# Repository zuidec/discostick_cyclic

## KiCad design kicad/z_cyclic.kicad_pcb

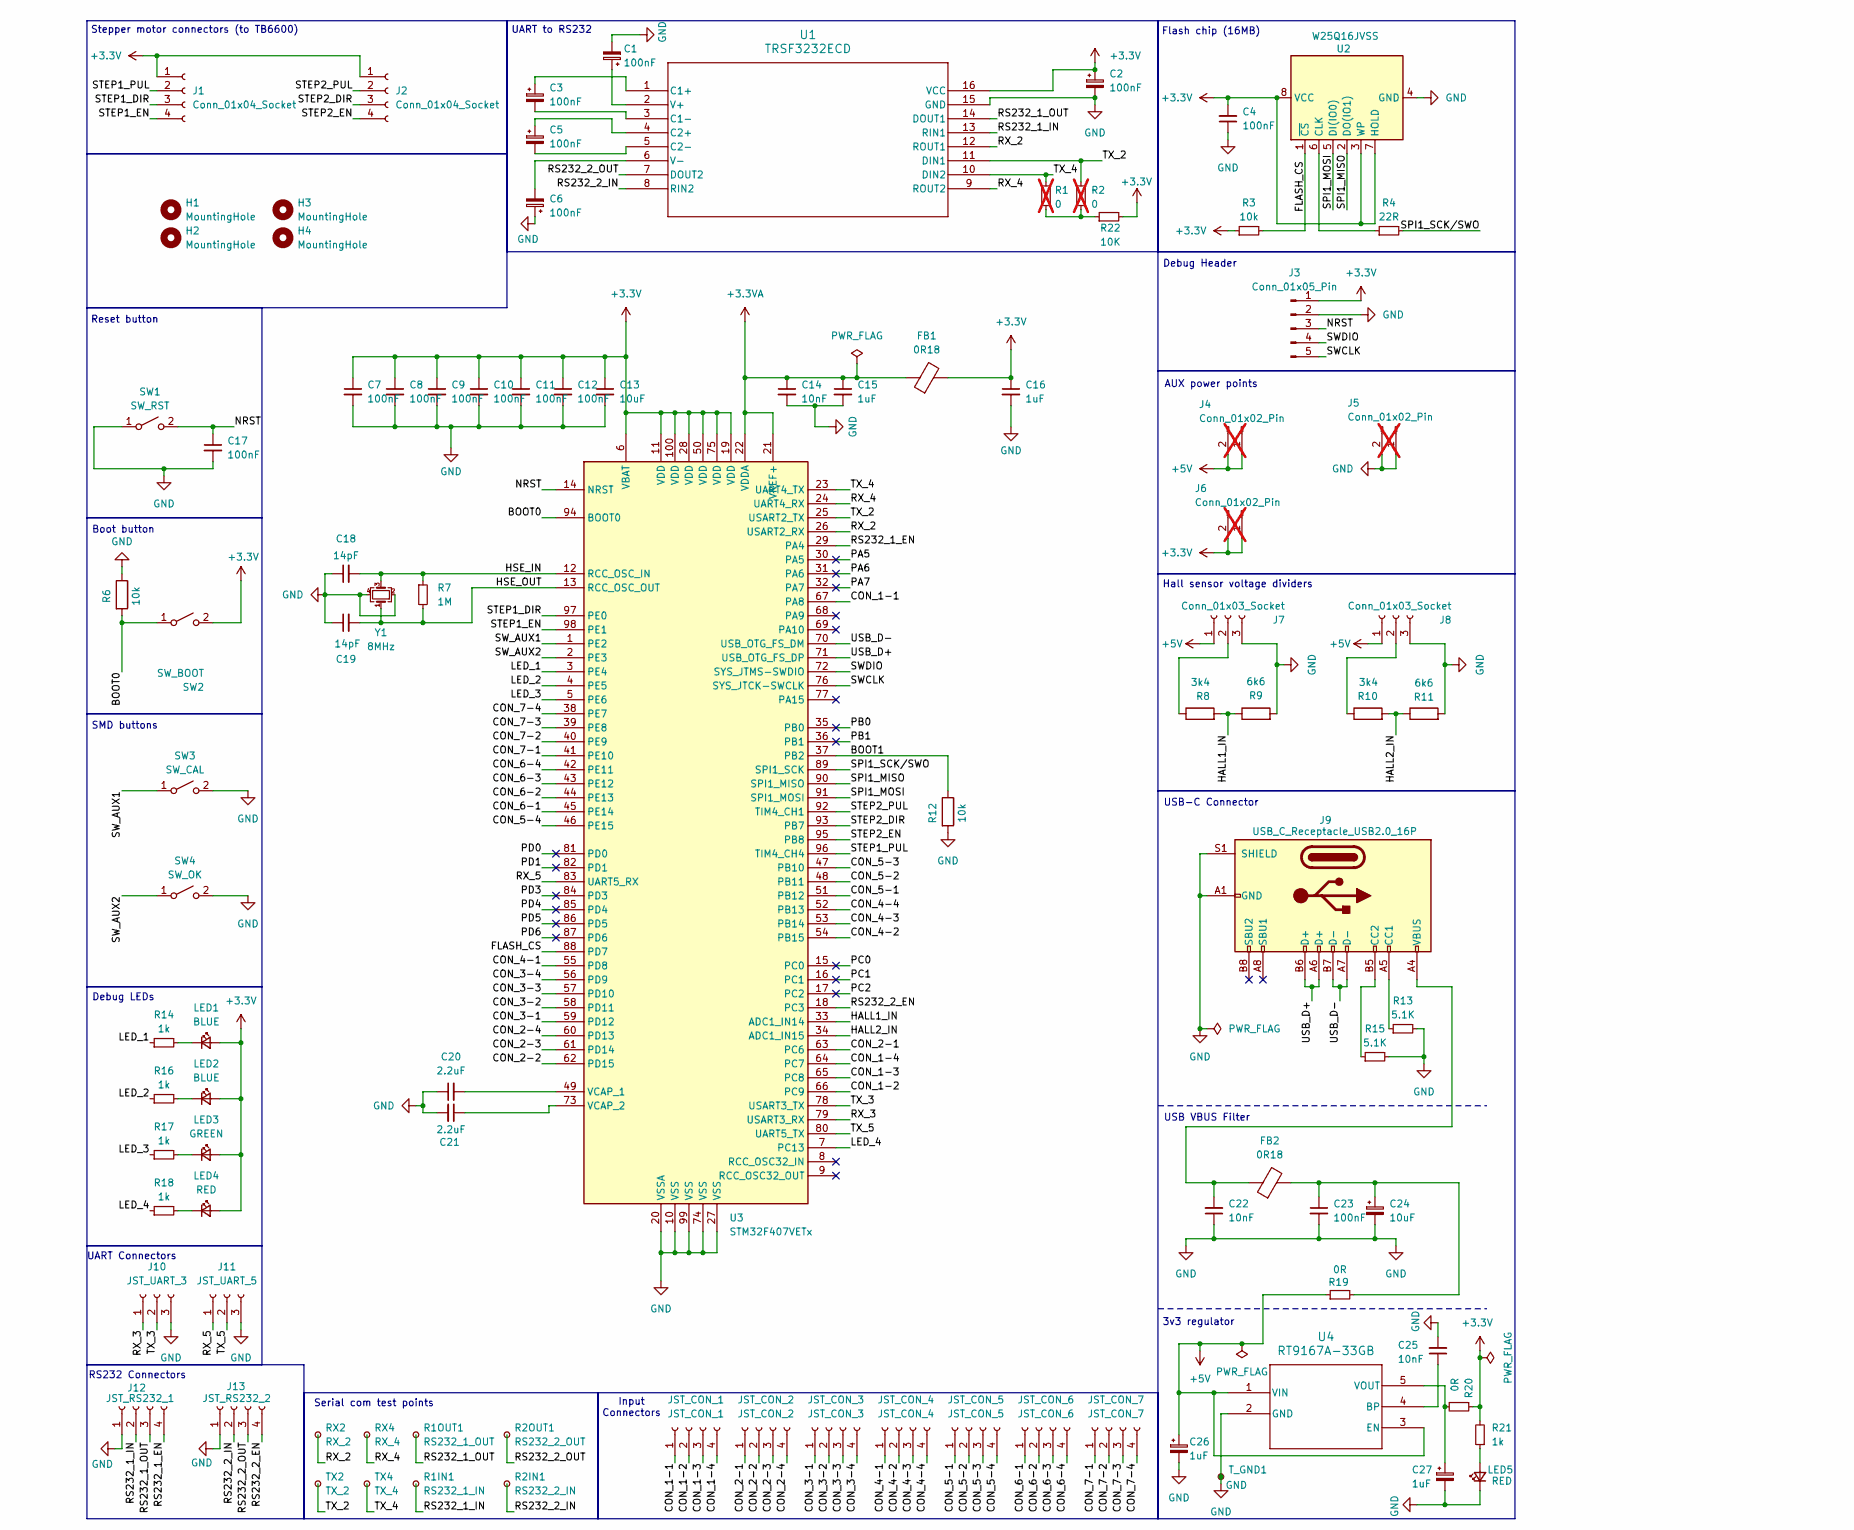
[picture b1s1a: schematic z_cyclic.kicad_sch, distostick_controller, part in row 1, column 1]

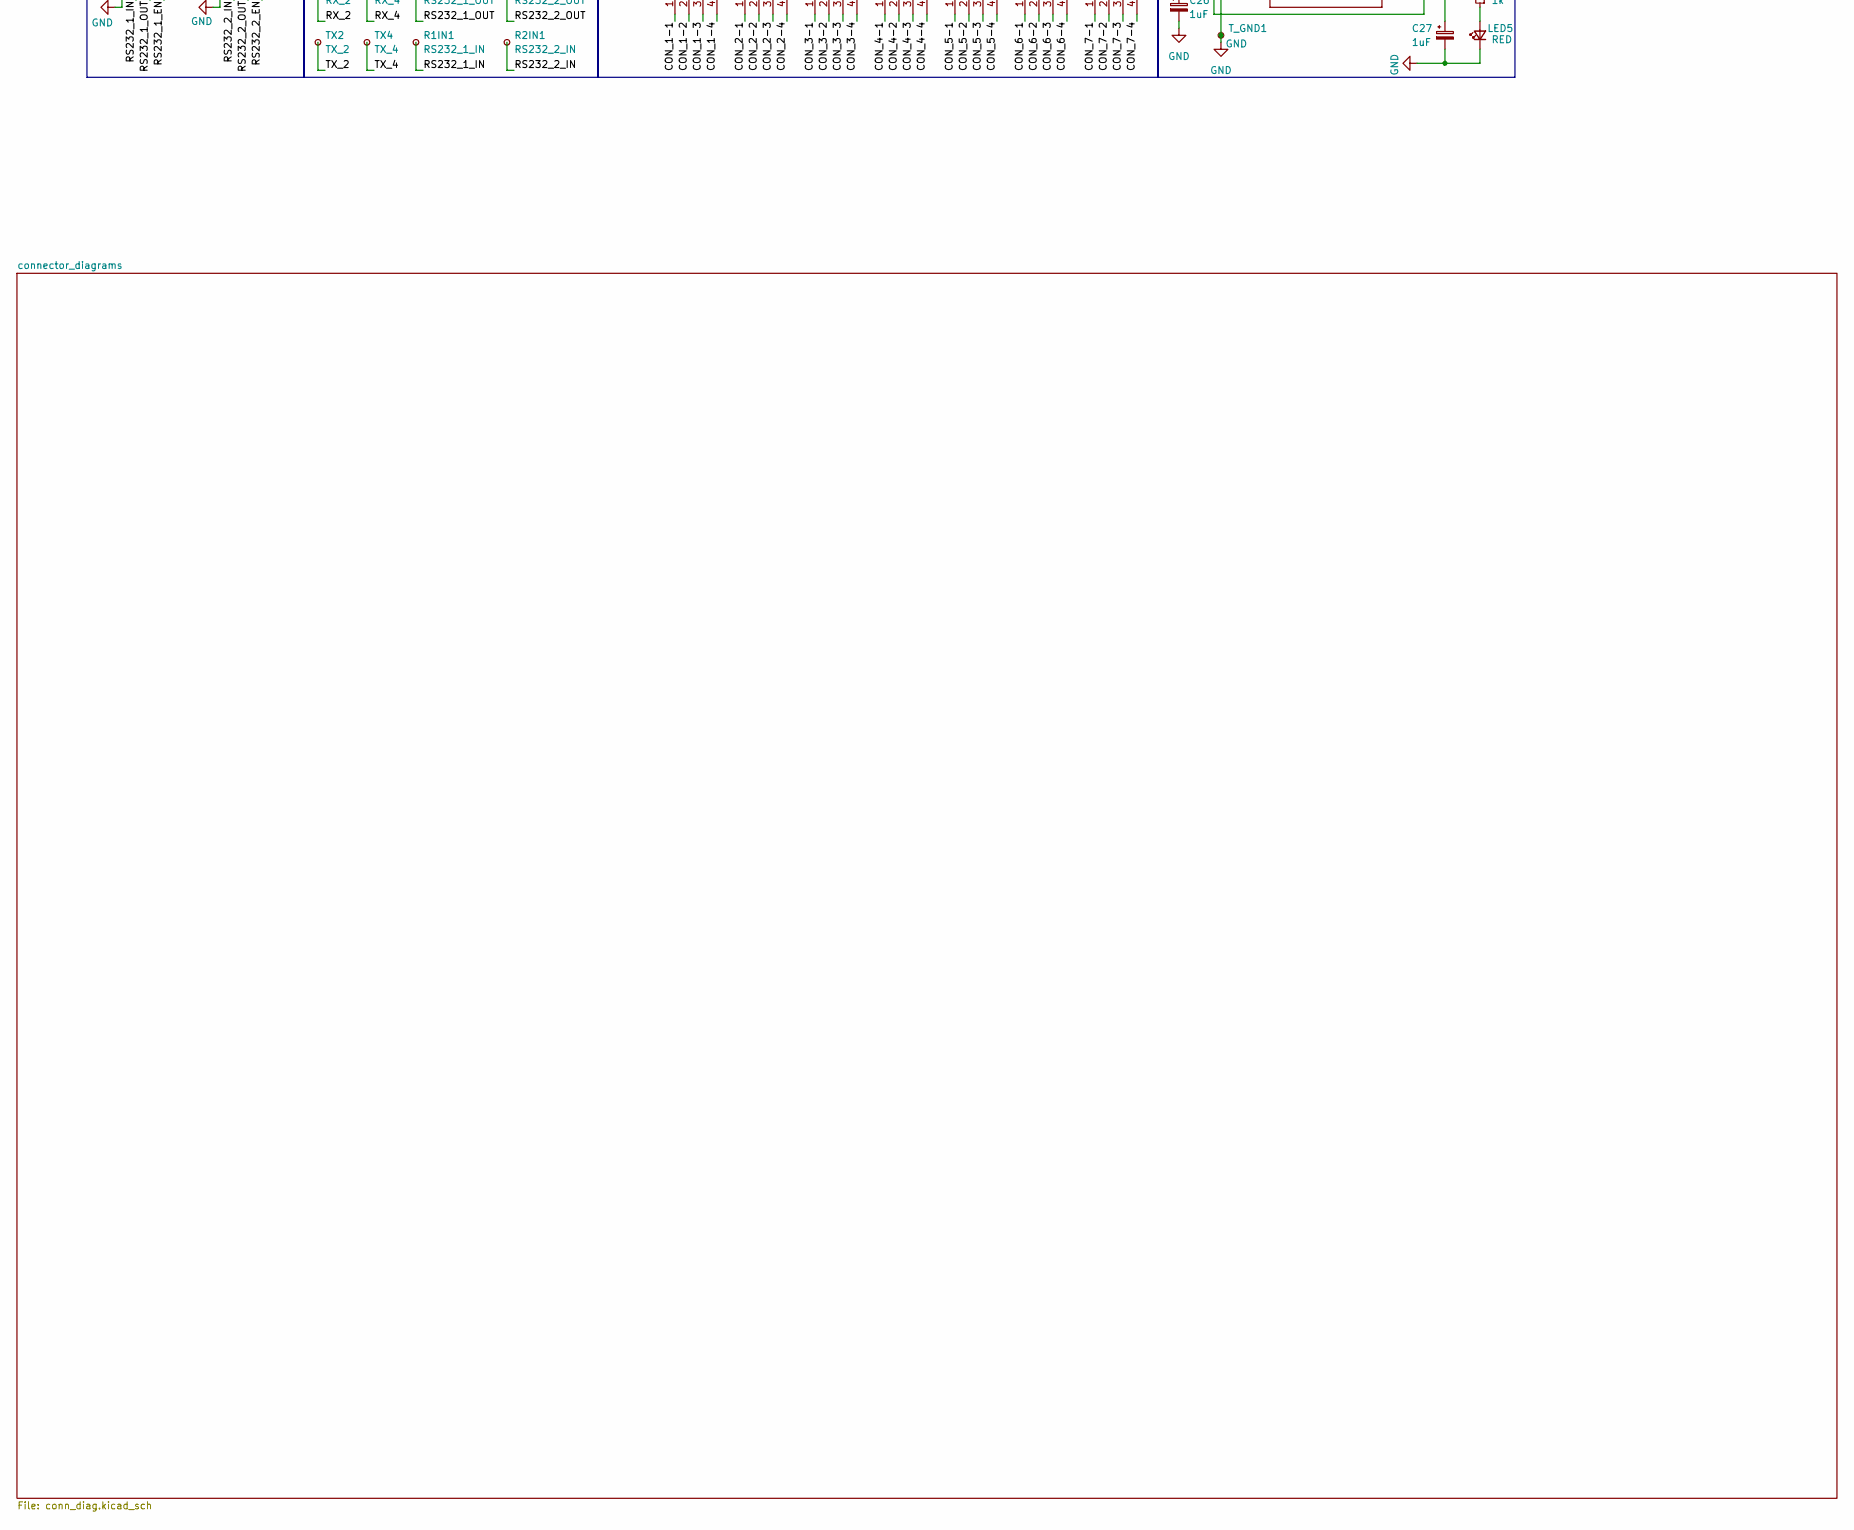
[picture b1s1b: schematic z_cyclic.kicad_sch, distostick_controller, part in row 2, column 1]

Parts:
C1, C2, C3, C4, C5, C6, C7, C8, C9, C10, C11, C12, C17, C23: 100nF; C_0402_1005Metric
C13, C24: 10uF; C_0603_1608Metric
C14, C22, C25: 10nF; C_0402_1005Metric
C15, C16, C26: 1uF; C_0402_1005Metric
C18, C19: 14pF; C_0402_1005Metric
C20, C21: 2.2uF; C_0402_1005Metric
C27: 1uF; C_0603_1608Metric
FB1, FB2: 0R18; R_0805_2012Metric
H1, H2, H3, H4: MountingHole; MountingHole_3.2mm_M3
J1, J2: Conn_01x04_Socket; JST_EH_B4B-EH-A_1x04_P2.50mm_Vertical
J3: Conn_01x05_Pin; PinHeader_1x05_P2.54mm_Vertical
J4, J5, J6: Conn_01x02_Pin; PinSocket_1x02_P2.54mm_Vertical; not fitted
J7, J8: Conn_01x03_Socket; JST_EH_B3B-EH-A_1x03_P2.50mm_Vertical
J9: USB_C_Receptacle_USB2.0_16P; USB_C_Receptacle_G-Switch_GT-USB-7010ASV
J10: JST_UART_3; JST_EH_B3B-EH-A_1x03_P2.50mm_Vertical
J11: JST_UART_5; JST_EH_B3B-EH-A_1x03_P2.50mm_Vertical
J12: JST_RS232_1; JST_EH_B4B-EH-A_1x04_P2.50mm_Vertical
J13: JST_RS232_2; JST_EH_B4B-EH-A_1x04_P2.50mm_Vertical
JST_CON_1: JST_CON_1; JST_EH_B4B-EH-A_1x04_P2.50mm_Vertical
JST_CON_2: JST_CON_2; JST_EH_B4B-EH-A_1x04_P2.50mm_Vertical
JST_CON_3: JST_CON_3; JST_EH_B4B-EH-A_1x04_P2.50mm_Vertical
JST_CON_4: JST_CON_4; JST_EH_B4B-EH-A_1x04_P2.50mm_Vertical
JST_CON_5: JST_CON_5; JST_EH_B4B-EH-A_1x04_P2.50mm_Vertical
JST_CON_6: JST_CON_6; JST_EH_B4B-EH-A_1x04_P2.50mm_Vertical
JST_CON_7: JST_CON_7; JST_EH_B4B-EH-A_1x04_P2.50mm_Vertical
LED1, LED2: BLUE; LED_0402_1005Metric
LED3: GREEN; LED_0402_1005Metric
LED4, LED5: RED; LED_0402_1005Metric
R1, R2: 0; R_0805_2012Metric_Pad1.20x1.40mm_HandSolder; not fitted
R1IN1: RS232_1_IN; TestPoint_Pad_D1.0mm
R1OUT1: RS232_1_OUT; TestPoint_Pad_D1.0mm
R2IN1: RS232_2_IN; TestPoint_Pad_D1.0mm
R2OUT1: RS232_2_OUT; TestPoint_Pad_D1.0mm
R3, R6, R12: 10k; R_0402_1005Metric
R4: 22R; R_0402_1005Metric
R7: 1M; R_0402_1005Metric
R8, R10: 3k4; R_0402_1005Metric
R9, R11: 6k6; R_0402_1005Metric
R13, R15: 5.1K; R_0402_1005Metric
R14, R16, R17, R18, R21: 1k; R_0402_1005Metric
R19, R20: 0R; SolderJumper-2_P1.3mm_Open_TrianglePad1.0x1.5mm
R22: 10K; R_0402_1005Metric
RX2: RX_2; TestPoint_Pad_D1.0mm
RX4: RX_4; TestPoint_Pad_D1.0mm
SW1: SW_RST; SW_SPST_B3U-1000P; PARTREV B
SW2: SW_BOOT; SW_SPST_B3U-1000P; PARTREV B
SW3: SW_CAL; SW_SPST_B3U-1000P; PARTREV B
SW4: SW_OK; SW_SPST_B3U-1000P; PARTREV B
TX2: TX_2; TestPoint_Pad_D1.0mm
TX4: TX_4; TestPoint_Pad_D1.0mm
T_GND1: GND; TestPoint_Pad_1.5x1.5mm
U1: TRSF3232ECD; D16
U2: W25Q16JVSS; SOIC-8_5.23x5.23mm_P1.27mm
U3: STM32F407VETx; LQFP-100_14x14mm_P0.5mm
U4: RT9167A-33GB; SOIC_A-33GB_RIT
Y1: 8MHz; Crystal_SMD_3225-4Pin_3.2x2.5mm

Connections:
+3.3V: C2.1, C4.2, C7.1, C8.1, C9.1, C10.1, C11.1, C12.1, C13.1, C16.1, FB1.2, J1.1, J2.1, J3.1, J6.1, J6.2, LED1.2 (A), LED2.2 (A), LED3.2 (A), LED4.2 (A), R3.1, R20.1, R21.2, R22.2, SW2.2 (B), U1.16 (VCC), U2.3 (WP), U2.7 (HOLD), U2.8 (VCC), U3.6 (VBAT), U3.11 (VDD), U3.19 (VDD), U3.28 (VDD), U3.50 (VDD), U3.75 (VDD), U3.100 (VDD)
+3.3VA: C14.1, C15.1, FB1.1, U3.21 (VREF+), U3.22 (VDDA)
+5V: C26.1, J4.1, J4.2, J7.1, J8.1, R19.1, U4.1 (VIN), U4.3 (EN)
/BOOT0: R6.2, SW2.1 (A), U3.94 (BOOT0)
/BOOT1: R12.1, U3.37 (PB2)
/CON_1-1: JST_CON_1.1, U3.67 (PA8)
/CON_1-2: JST_CON_1.2, U3.66 (PC9)
/CON_1-3: JST_CON_1.3, U3.65 (PC8)
/CON_1-4: JST_CON_1.4, U3.64 (PC7)
/CON_2-1: JST_CON_2.1, U3.63 (PC6)
/CON_2-2: JST_CON_2.2, U3.62 (PD15)
/CON_2-3: JST_CON_2.3, U3.61 (PD14)
/CON_2-4: JST_CON_2.4, U3.60 (PD13)
/CON_3-1: JST_CON_3.1, U3.59 (PD12)
/CON_3-2: JST_CON_3.2, U3.58 (PD11)
/CON_3-3: JST_CON_3.3, U3.57 (PD10)
/CON_3-4: JST_CON_3.4, U3.56 (PD9)
/CON_4-1: JST_CON_4.1, U3.55 (PD8)
/CON_4-2: JST_CON_4.2, U3.54 (PB15)
/CON_4-3: JST_CON_4.3, U3.53 (PB14)
/CON_4-4: JST_CON_4.4, U3.52 (PB13)
/CON_5-1: JST_CON_5.1, U3.51 (PB12)
/CON_5-2: JST_CON_5.2, U3.48 (PB11)
/CON_5-3: JST_CON_5.3, U3.47 (PB10)
/CON_5-4: JST_CON_5.4, U3.46 (PE15)
/CON_6-1: JST_CON_6.1, U3.45 (PE14)
/CON_6-2: JST_CON_6.2, U3.44 (PE13)
/CON_6-3: JST_CON_6.3, U3.43 (PE12)
/CON_6-4: JST_CON_6.4, U3.42 (PE11)
/CON_7-1: JST_CON_7.1, U3.41 (PE10)
/CON_7-2: JST_CON_7.2, U3.40 (PE9)
/CON_7-3: JST_CON_7.3, U3.39 (PE8)
/CON_7-4: JST_CON_7.4, U3.38 (PE7)
/FLASH_CS: R3.2, U2.1 (~CS), U3.88 (PD7)
/HALL1_IN: R8.2, R9.1, U3.33 (ADC1_IN14)
/HALL2_IN: R10.2, R11.1, U3.34 (ADC1_IN15)
/HSE_IN: C18.2, R7.1, U3.12 (RCC_OSC_IN), Y1.3
/HSE_OUT: C19.2, R7.2, U3.13 (RCC_OSC_OUT), Y1.1
/LED_1: R14.1, U3.3 (PE4)
/LED_2: R16.1, U3.4 (PE5)
/LED_3: R17.1, U3.5 (PE6)
/LED_4: R18.1, U3.7 (PC13)
/NRST: C17.1, J3.3, SW1.2 (B), U3.14 (NRST)
/PA5: U3.30 (PA5)
/PA6: U3.31 (PA6)
/PA7: U3.32 (PA7)
/PB0: U3.35 (PB0)
/PB1: U3.36 (PB1)
/PC0: U3.15 (PC0)
/PC1: U3.16 (PC1)
/PC2: U3.17 (PC2)
/PD0: U3.81 (PD0)
/PD1: U3.82 (PD1)
/PD3: U3.84 (PD3)
/PD4: U3.85 (PD4)
/PD5: U3.86 (PD5)
/PD6: U3.87 (PD6)
/RS232_1_EN: J12.4, U3.29 (PA4)
/RS232_1_IN: J12.2, R1IN1.1, U1.13 (RIN1)
/RS232_1_OUT: J12.3, R1OUT1.1, U1.14 (DOUT1)
/RS232_2_EN: J13.4, U3.18 (PC3)
/RS232_2_IN: J13.2, R2IN1.1, U1.8 (RIN2)
/RS232_2_OUT: J13.3, R2OUT1.1, U1.7 (DOUT2)
/RX_2: RX2.1, U1.12 (ROUT1), U3.26 (USART2_RX)
/RX_3: J10.1, U3.79 (USART3_RX)
/RX_4: RX4.1, U1.9 (ROUT2), U3.24 (UART4_RX)
/RX_5: J11.1, U3.83 (UART5_RX)
/SPI1_MISO: U2.2 (DO(IO1)), U3.90 (SPI1_MISO)
/SPI1_MOSI: U2.5 (DI(IO0)), U3.91 (SPI1_MOSI)
/SPI1_SCK/SWO: R4.2, U3.89 (SPI1_SCK)
/STEP1_DIR: J1.3, U3.97 (PE0)
/STEP1_EN: J1.4, U3.98 (PE1)
/STEP1_PUL: J1.2, U3.96 (TIM4_CH4)
/STEP2_DIR: J2.3, U3.93 (PB7)
/STEP2_EN: J2.4, U3.95 (PB8)
/STEP2_PUL: J2.2, U3.92 (TIM4_CH1)
/SWCLK: J3.5, U3.76 (SYS_JTCK-SWCLK)
/SWDIO: J3.4, U3.72 (SYS_JTMS-SWDIO)
/SW_AUX1: SW3.1 (A), U3.1 (PE2)
/SW_AUX2: SW4.1 (A), U3.2 (PE3)
/TX_2: R2.1, TX2.1, U1.11 (DIN1), U3.25 (USART2_TX)
/TX_3: J10.2, U3.78 (USART3_TX)
/TX_4: R1.1, TX4.1, U1.10 (DIN2), U3.23 (UART4_TX)
/TX_5: J11.2, U3.80 (UART5_TX)
/USB_D+: J9.A6 (D+), J9.B6 (D+), U3.71 (USB_OTG_FS_DP)
/USB_D-: J9.A7 (D-), J9.B7 (D-), U3.70 (USB_OTG_FS_DM)
GND: C1.2, C2.2, C4.1, C6.1, C7.2, C8.2, C9.2, C10.2, C11.2, C12.2, C13.2, C14.2, C15.2, C16.2, C17.2, C18.1, C19.1, C20.1, C21.2, C22.1, C23.2, C24.2, C25.2, C26.2, C27.2, J3.2, J5.1, J5.2, J7.3, J8.3, J9.A1 (GND), J9.A12 (GND), J9.B1 (GND), J9.B12 (GND), J9.S1 (SHIELD), J10.3, J11.3, J12.1, J13.1, LED5.1 (K), R6.1, R9.2, R11.2, R12.2, R13.2, R15.2, SW1.1 (A), SW3.2 (B), SW4.2 (B), T_GND1.1, U1.15 (GND), U2.4 (GND), U3.10 (VSS), U3.20 (VSSA), U3.27 (VSS), U3.74 (VSS), U3.99 (VSS), U4.2 (GND), Y1.2, Y1.4
unnamed: C22.2, FB2.1, J9.A4 (VBUS), J9.A9 (VBUS), J9.B4 (VBUS), J9.B9 (VBUS)
unnamed: C23.1, C24.1, FB2.2, R19.2
unnamed: J7.2, R8.1
unnamed: J8.2, R10.1
unnamed: J9.A5 (CC1), R13.1
unnamed: J9.B5 (CC2), R15.1
unnamed: LED1.1 (K), R14.2
unnamed: LED2.1 (K), R16.2
unnamed: LED3.1 (K), R17.2
unnamed: LED4.1 (K), R18.2
unnamed: LED5.2 (A), R21.1
unnamed: R1.2, R2.2, R22.1
unnamed: C3.1, U1.1 (C1+)
unnamed: C3.2, U1.3 (C1-)
unnamed: C5.1, U1.4 (C2+)
unnamed: C5.2, U1.5 (C2-)
unnamed: C1.1, U1.2 (V+)
unnamed: C6.2, U1.6 (V-)
unnamed: R4.1, U2.6 (CLK)
unnamed: C20.2, U3.49 (VCAP_1)
unnamed: C21.1, U3.73 (VCAP_2)
unnamed: C25.1, U4.4 (BP)
unnamed: C27.1, R20.2, U4.5 (VOUT)

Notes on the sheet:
Stepper motor connectors (to TB6600)
Reset button
RS232 Connectors
SMD buttons
Boot button
UART to RS232
Serial com test points
Flash chip (16MB)
AUX power points
3v3 regulator
USB VBUS Filter
USB-C Connector
Debug LEDs
UART Connectors
Input Connectors
Hall sensor voltage dividers
Debug Header

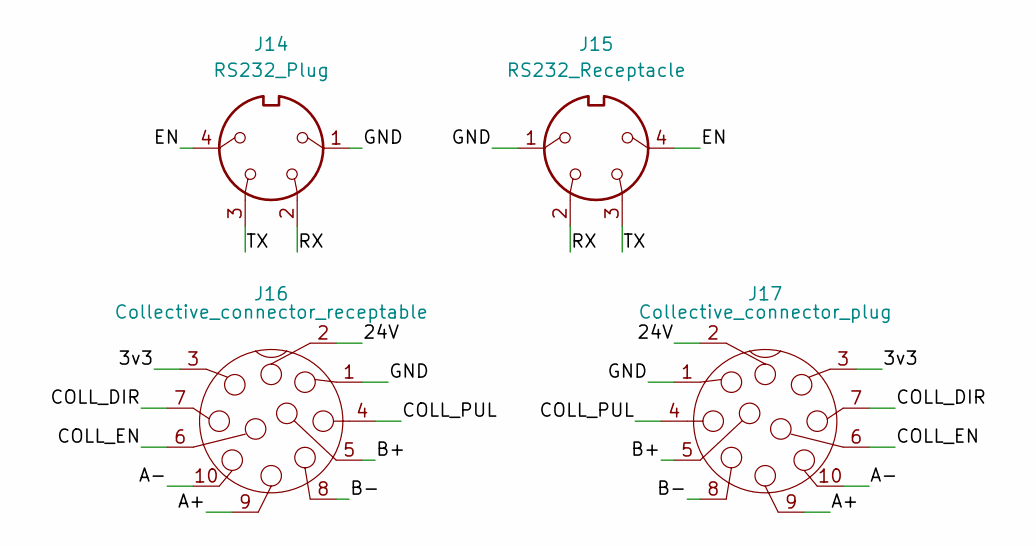
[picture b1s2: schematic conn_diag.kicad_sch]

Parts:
J14: RS232_Plug
J15: RS232_Receptacle
J16: Collective_connector_receptable
J17: Collective_connector_plug

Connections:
unnamed: J14.1, J15.1, J16.1, J17.1
unnamed: J14.2, J15.2
unnamed: J14.3, J15.3
unnamed: J14.4, J15.4
unnamed: J16.2, J17.2
unnamed: J16.3, J17.3
unnamed: J16.4, J17.4
unnamed: J16.5, J17.5
unnamed: J16.6, J17.6
unnamed: J16.7, J17.7
unnamed: J16.8, J17.8
unnamed: J16.9, J17.9
unnamed: J16.10, J17.10

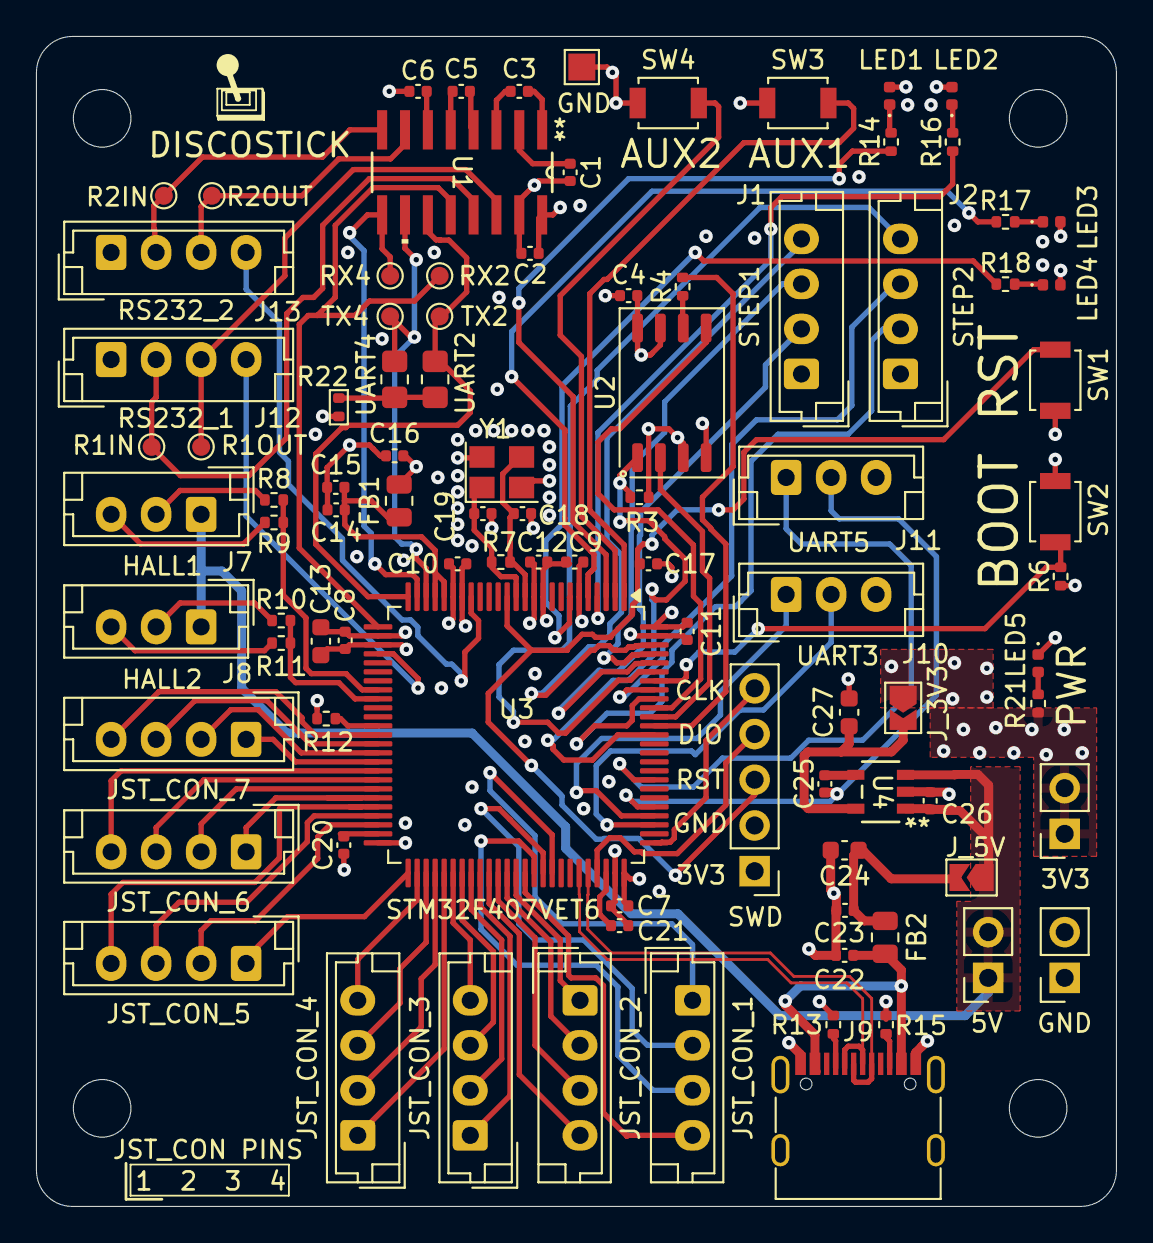
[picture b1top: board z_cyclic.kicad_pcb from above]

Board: 4 copper layers, 60.0 x 65.0 mm, 97 parts (0 on the bottom side), 96 nets.

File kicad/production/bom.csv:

Designator,Footprint,Quantity,Value,LCSC Part #
"C1, C10, C11, C12, C17, C2, C23, C3, C4, C5, C6, C7, C8, C9",402,14,100nF,C513772
"C13, C24",603,2,10uF,C344022
"C14, C22, C25",402,3,10nF,C60133
"C15, C16, C26",402,3,1uF,C14445
"C18, C19",402,2,14pF,C458857
"C20, C21",402,2,2.2uF,C385032
C27,603,1,1uF,C2918486
"FB1, FB2",805,2,0R18,C74480
"J1, J2",JST_EH_B4B-EH-A_1x04_P2.50mm_Vertical,2,Conn_01x04_Socket,C160258
J10,JST_EH_B3B-EH-A_1x03_P2.50mm_Vertical,1,JST_UART_3,C398546
J11,JST_EH_B3B-EH-A_1x03_P2.50mm_Vertical,1,JST_UART_5,C398546
J12,JST_EH_B4B-EH-A_1x04_P2.50mm_Vertical,1,JST_RS232_1,C160258
J13,JST_EH_B4B-EH-A_1x04_P2.50mm_Vertical,1,JST_RS232_2,C160258
"J7, J8",JST_EH_B3B-EH-A_1x03_P2.50mm_Vertical,2,Conn_01x03_Socket,C398546
J9,USB_C_Receptacle_G-Switch_GT-USB-7010ASV,1,USB_C_Receptacle_USB2.0_16P,C2988369
JST_CON_1,JST_EH_B4B-EH-A_1x04_P2.50mm_Vertical,1,JST_CON_1,C160258
JST_CON_2,JST_EH_B4B-EH-A_1x04_P2.50mm_Vertical,1,JST_CON_2,C160258
JST_CON_3,JST_EH_B4B-EH-A_1x04_P2.50mm_Vertical,1,JST_CON_3,C160258
JST_CON_4,JST_EH_B4B-EH-A_1x04_P2.50mm_Vertical,1,JST_CON_4,C160258
JST_CON_5,JST_EH_B4B-EH-A_1x04_P2.50mm_Vertical,1,JST_CON_5,C160258
JST_CON_6,JST_EH_B4B-EH-A_1x04_P2.50mm_Vertical,1,JST_CON_6,C160258
JST_CON_7,JST_EH_B4B-EH-A_1x04_P2.50mm_Vertical,1,JST_CON_7,C160258
"LED1, LED2",402,2,BLUE,C2844007
LED3,402,1,GREEN,C2980183
"LED4, LED5",402,2,RED,C136765
"R10, R8",402,2,3k4,C3013164
"R11, R9",402,2,6k6,C853381
"R12, R22, R3, R6",402,4,10k,C60490
"R13, R15",402,2,5.1K,C25905
"R14, R16, R17, R18, R21",402,5,1k,C106235
R4,402,1,22R,C114765
R7,402,1,1M,C138033
SW1,SW_SPST_B3U-1000P,1,SW_RST,C231329
SW2,SW_SPST_B3U-1000P,1,SW_BOOT,C231329
SW3,SW_SPST_B3U-1000P,1,SW_CAL,C231329
SW4,SW_SPST_B3U-1000P,1,SW_OK,C231329
U2,SOIC-8_5.23x5.23mm_P1.27mm,1,W25Q16JVSS,C131025
U4,SOIC_A-33GB_RIT,1,RT9167A-33GB,C113513
Y1,Crystal_SMD_3225-4Pin_3.2x2.5mm,1,8MHz,C2835958

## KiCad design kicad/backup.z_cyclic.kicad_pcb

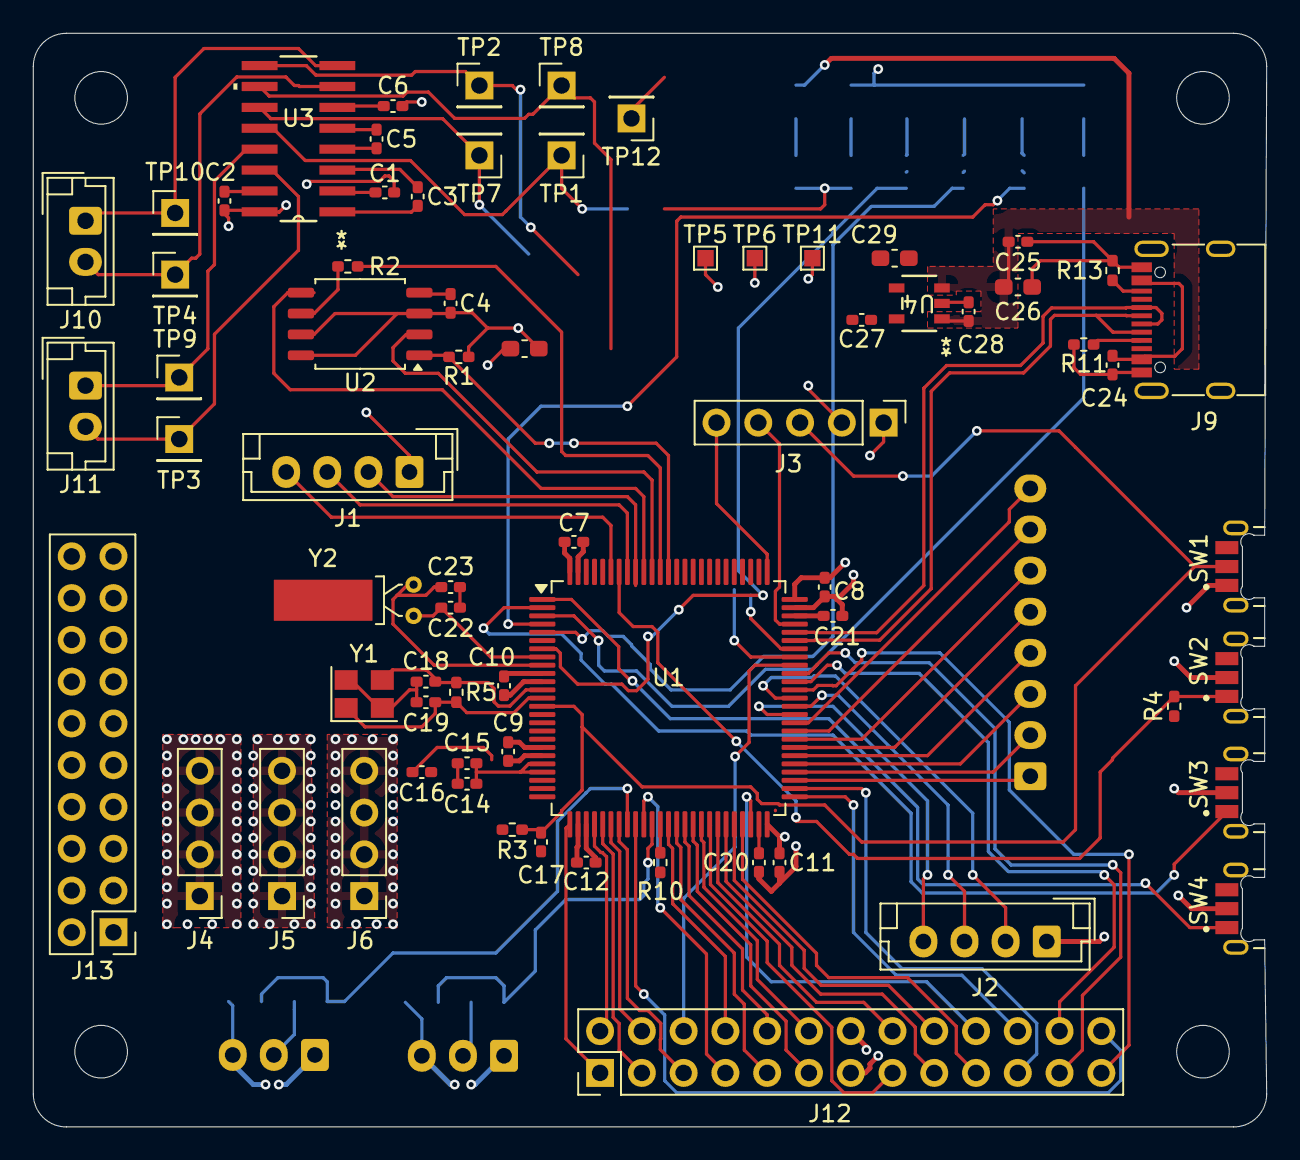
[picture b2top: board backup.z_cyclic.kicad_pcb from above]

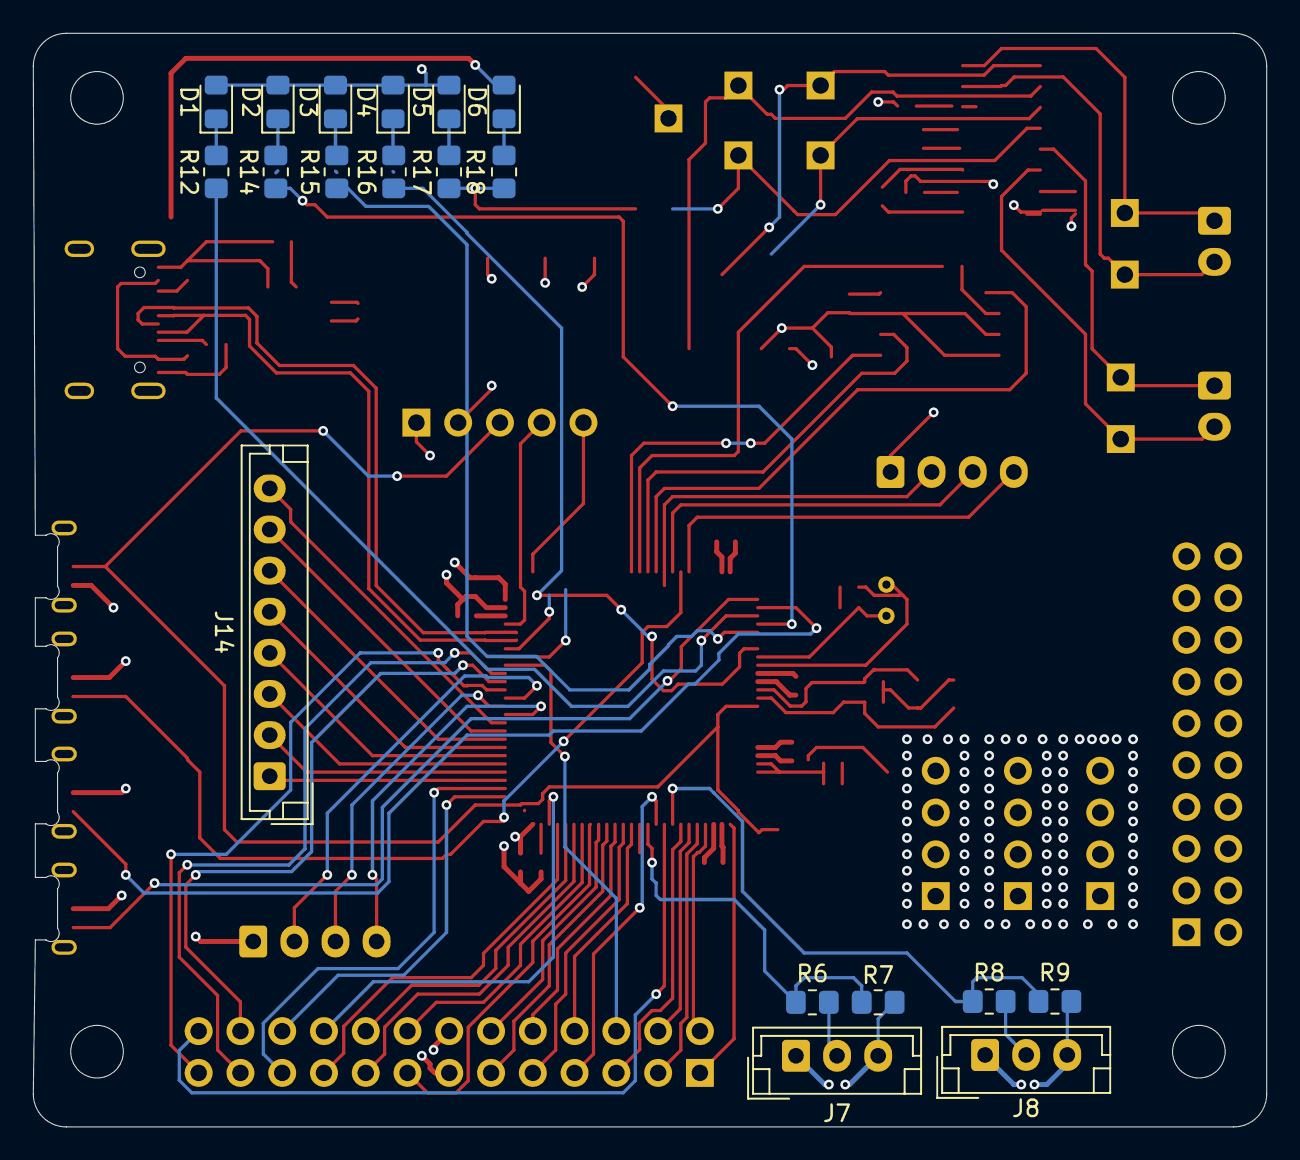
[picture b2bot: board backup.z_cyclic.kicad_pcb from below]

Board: 4 copper layers, 75.0 x 66.5 mm, 93 parts (19 on the bottom side), 112 nets.

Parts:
C1, C2, C3, C4, C5, C6, C7, C8, C9, C10, C11, C12, C17, C25: 100nF; C_0402_1005Metric_Pad0.74x0.62mm_HandSolder
C13, C26: 10uF; C_0603_1608Metric_Pad1.08x0.95mm_HandSolder
C14, C24: 10nF; C_0402_1005Metric_Pad0.74x0.62mm_HandSolder
C15, C16, C28: 1uF; C_0402_1005Metric_Pad0.74x0.62mm_HandSolder
C18, C19: 14pF; C_0402_1005Metric_Pad0.74x0.62mm_HandSolder
C20, C21: 2.2uF; C_0402_1005Metric_Pad0.74x0.62mm_HandSolder
C22, C23: 1.5pF; C_0402_1005Metric_Pad0.74x0.62mm_HandSolder
C27: 10uF; C_0402_1005Metric_Pad0.74x0.62mm_HandSolder
C29: 1uF; C_0603_1608Metric_Pad1.08x0.95mm_HandSolder
D1, D2: BLUE; LED_0805_2012Metric_Pad1.15x1.40mm_HandSolder
D3: GREEN; LED_0805_2012Metric_Pad1.15x1.40mm_HandSolder
D4, D5, D6: RED; LED_0805_2012Metric_Pad1.15x1.40mm_HandSolder
H1, H2, H3, H4: MountingHole; MountingHole_3.2mm_M3
J1, J2: Conn_01x04_Socket; JST_EH_B4B-EH-A_1x04_P2.50mm_Vertical
J3: Conn_01x05_Pin; PinHeader_1x05_P2.54mm_Vertical
J4, J5, J6: Conn_01x04_Socket; PinHeader_1x04_P2.54mm_Vertical
J7, J8: Conn_01x03_Socket; JST_EH_B3B-EH-A_1x03_P2.50mm_Vertical
J9: USB_C_Receptacle_USB2.0_16P; USB_C_Receptacle_G-Switch_GT-USB-7010ASV
J10, J11: Conn_01x02_Socket; JST_EH_B2B-EH-A_1x02_P2.50mm_Vertical
J12: Conn_02x13_Counter_Clockwise; PinHeader_2x13_P2.54mm_Vertical
J13: Conn_02x10_Counter_Clockwise; PinHeader_2x10_P2.54mm_Vertical
J14: Conn_01x08_Socket; JST_EH_B8B-EH-A_1x08_P2.50mm_Vertical
R1, R4, R10: 10k; R_0402_1005Metric_Pad0.72x0.64mm_HandSolder
R2: 22R; R_0402_1005Metric_Pad0.72x0.64mm_HandSolder
R3: 10K; R_0402_1005Metric_Pad0.72x0.64mm_HandSolder
R5: 1M; R_0402_1005Metric_Pad0.72x0.64mm_HandSolder
R6, R8: 3k4; R_0805_2012Metric_Pad1.20x1.40mm_HandSolder
R7, R9: 6k6; R_0805_2012Metric_Pad1.20x1.40mm_HandSolder
R11, R13: 5.1K; R_0402_1005Metric_Pad0.72x0.64mm_HandSolder
R12, R14, R15, R16, R17, R18: 1k; R_0805_2012Metric_Pad1.20x1.40mm_HandSolder
SW1: SW_RST; SW_PTS847MM160LSMTR2_LFS
SW2: SW_BOOT; SW_PTS847MM160LSMTR2_LFS
SW3: SW_CAL; SW_PTS847MM160LSMTR2_LFS
SW4: SW_OK; SW_PTS847MM160LSMTR2_LFS
TP1: RX_1; PinHeader_1x01_P2.54mm_Vertical
TP2: RX_3; PinHeader_1x01_P2.54mm_Vertical
TP3: RS232_1_OUT; PinHeader_1x01_P2.54mm_Vertical
TP4: RS232_2_OUT; PinHeader_1x01_P2.54mm_Vertical
TP5: 3V3; TestPoint_Pad_1.0x1.0mm
TP6: 5V; TestPoint_Pad_1.0x1.0mm
TP7: TX_1; PinHeader_1x01_P2.54mm_Vertical
TP8: TX_3; PinHeader_1x01_P2.54mm_Vertical
TP9: RS232_1_IN; PinHeader_1x01_P2.54mm_Vertical
TP10: RS232_2_IN; PinHeader_1x01_P2.54mm_Vertical
TP11: GND; TestPoint_Pad_1.0x1.0mm
TP12: GND; PinHeader_1x01_P2.54mm_Vertical
U1: STM32F407VETx; LQFP-100_14x14mm_P0.5mm
U2: W25Q16JVSS; SOIC-8_5.23x5.23mm_P1.27mm
U3: TRSF3232ECD; D16
U4: RT9167A-33GB; SOIC_A-33GB_RIT
Y1: 8MHz; Crystal_SMD_3225-4Pin_3.2x2.5mm
Y2: 32.768K; Crystal_DS26_D2.0mm_L6.0mm_Horizontal_1EP_style1

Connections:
+3.3V: C2.1, C4.2, C7.1, C8.1, C9.1, C10.1, C11.1, C12.1, C13.1, C16.1, C29.1, D1.2 (A), D2.2 (A), D3.2 (A), D4.2 (A), D5.2 (A), J1.1, J2.1, J3.1, J6.1, J6.2, J6.3, J6.4, J12.13, J13.10, R1.1, R3.1, SW2.2, TP5.1, U1.6 (VBAT), U1.11 (VDD), U1.19 (VDD), U1.28 (VDD), U1.50 (VDD), U1.75 (VDD), U1.100 (VDD), U2.3 (WP), U2.7 (HOLD), U2.8 (VCC), U3.16 (VCC), U4.4 (VOUT)
+3.3VA: C14.1, C15.1, U1.21 (VREF+), U1.22 (VDDA)
+5V: C25.1, C26.1, C28.1, D6.2 (A), J4.1, J4.2, J4.3, J4.4, J7.1, J8.1, TP6.1, U4.1 (VIN), U4.3 (EN)
/AP_REL: J14.8, U1.60 (PD13)
/BOOT0: R4.2, SW2.1, U1.94 (BOOT0)
/BOOT1: R10.1, U1.37 (PB2)
/CARGO_REL: J14.7, U1.59 (PD12)
/CD_REL: J14.5, U1.57 (PD10)
/FLASH_CS: R1.2, U1.88 (PD7), U2.1 (~CS)
/HAT_D: J14.1, U1.53 (PB14)
/HAT_L: J14.4, U1.56 (PD9)
/HAT_R: J14.3, U1.55 (PD8)
/HAT_U: J14.2, U1.54 (PB15)
/HSE_IN: C18.2, R5.1, U1.12 (RCC_OSC_IN), Y1.3
/HSE_OUT: C19.2, R5.2, U1.13 (RCC_OSC_OUT), Y1.1
/ICS_SW: J14.6, U1.58 (PD11)
/LED_AUX: R16.1, U1.7 (PC13)
/LED_PITCH: R14.1, U1.4 (PE5)
/LED_ROLL: R12.1, U1.3 (PE4)
/LED_STATUS: R15.1, U1.5 (PE6)
/NRST: C17.1, J3.3, R3.2, SW1.2, U1.14 (NRST)
/PA0: J13.5, U1.23 (PA0)
/PA1: J13.6, U1.24 (PA1)
/PA2: J13.7, U1.25 (PA2)
/PA3: J12.1, U1.26 (PA3)
/PA4: J12.2, U1.29 (PA4)
/PA5: J12.3, U1.30 (PA5)
/PA6: J12.4, U1.31 (PA6)
/PA7: J12.5, U1.32 (PA7)
/PA8: J12.6, U1.67 (PA8)
/PB0: J12.7, U1.35 (PB0)
/PB9: J13.20, U1.96 (PB9)
/PB10: J12.19, U1.47 (PB10)
/PB11: J12.20, U1.48 (PB11)
/PB12: J12.22, U1.51 (PB12)
/PB13: J12.21, U1.52 (PB13)
/PC0: J13.1, U1.15 (PC0)
/PC1: J13.2, U1.16 (PC1)
/PC2: J13.3, U1.17 (PC2)
/PC3: J13.4, U1.18 (PC3)
/PC5: J12.26, U1.34 (PC5)
/PC7: J12.25, U1.64 (PC7)
/PC8: J12.24, U1.65 (PC8)
/PC9: J12.23, U1.66 (PC9)
/PC12: J13.12, U1.80 (PC12)
/PD0: J13.13, U1.81 (PD0)
/PD1: J13.14, U1.82 (PD1)
/PD2: J13.15, U1.83 (PD2)
/PD3: J13.16, U1.84 (PD3)
/PD4: J13.17, U1.85 (PD4)
/PD5: J13.18, U1.86 (PD5)
/PD6: J13.19, U1.87 (PD6)
/PE0: J13.8, U1.97 (PE0)
/PE1: J13.9, U1.98 (PE1)
/PE7: J12.8, U1.38 (PE7)
/PE8: J12.9, U1.39 (PE8)
/PE9: J12.10, U1.40 (PE9)
/PE10: J12.11, U1.41 (PE10)
/PE11: J12.12, U1.42 (PE11)
/PE12: J12.15, U1.43 (PE12)
/PE13: J12.16, U1.44 (PE13)
/PE14: J12.17, U1.45 (PE14)
/PE15: J12.18, U1.46 (PE15)
/PITCH_DIR: J1.3, U1.93 (PB7)
/PITCH_EN: J1.4, U1.95 (PB8)
/PITCH_IN: R6.2, R7.1, U1.36 (ADC1_IN9)
/PITCH_PUL: J1.2, U1.92 (TIM4_CH1)
/ROLL_DIR: J2.3, U1.62 (PD15)
/ROLL_EN: J2.4, U1.61 (PD14)
/ROLL_IN: R8.2, R9.1, U1.33 (ADC1_IN14)
/ROLL_PUL: J2.2, U1.63 (TIM3_CH1)
/RS232_1_IN: J11.1, TP9.1, U3.13 (RIN1)
/RS232_1_OUT: J11.2, TP3.1, U3.14 (DOUT1)
/RS232_2_IN: J10.1, TP10.1, U3.8 (RIN2)
/RS232_2_OUT: J10.2, TP4.1, U3.7 (DOUT2)
/RX_1: TP1.1, U1.69 (USART1_RX), U3.12 (ROUT1)
/RX_3: TP2.1, U1.79 (USART3_RX), U3.9 (ROUT2)
/SPI1_MISO: U1.90 (SPI1_MISO), U2.2 (DO(IO1))
/SPI1_MOSI: U1.91 (SPI1_MOSI), U2.5 (DI(IO0))
/SPI1_SCK/SWO: R2.2, U1.89 (SPI1_SCK)
/SWCLK: J3.5, U1.76 (SYS_JTCK-SWCLK)
/SWDIO: J3.4, U1.72 (SYS_JTMS-SWDIO)
/SW_CAL: SW3.1, U1.2 (PE3)
/SW_OK: SW4.1, U1.1 (PE2)
/TX_1: TP7.1, U1.68 (USART1_TX), U3.11 (DIN1)
/TX_3: TP8.1, U1.78 (USART3_TX), U3.10 (DIN2)
/USB_D+: J9.A6 (D+), J9.B6 (D+), U1.71 (USB_OTG_FS_DP)
/USB_D-: J9.A7 (D-), J9.B7 (D-), U1.70 (USB_OTG_FS_DM)
GND: C1.2, C2.2, C4.1, C6.1, C7.2, C8.2, C9.2, C10.2, C11.2, C12.2, C13.2, C14.2, C15.2, C16.2, C17.2, C18.1, C19.1, C20.1, C21.2, C22.2, C23.2, C24.1, C25.2, C26.2, C27.2, C28.2, C29.2, J3.2, J5.1, J5.2, J5.3, J5.4, J7.3, J8.3, J9.A1 (GND), J9.A12 (GND), J9.B1 (GND), J9.B12 (GND), J9.S1 (SHIELD), J12.14, J13.11, R4.1, R7.2, R9.2, R10.2, R11.2, R13.2, R17.1, R18.2, SW1.1, SW3.2, SW4.2, TP11.1, TP12.1, U1.10 (VSS), U1.20 (VSSA), U1.27 (VSS), U1.74 (VSS), U1.99 (VSS), U2.4 (GND), U3.15 (GND), U4.2 (GND), Y1.2, Y1.4
unnamed: C24.2, J9.A4 (VBUS), J9.A9 (VBUS), J9.B4 (VBUS), J9.B9 (VBUS)
unnamed: D1.1 (K), R12.2
unnamed: D2.1 (K), R14.2
unnamed: D3.1 (K), R15.2
unnamed: D4.1 (K), R16.2
unnamed: D5.1 (K), R17.2
unnamed: D6.1 (K), R18.1
unnamed: J7.2, R6.1
unnamed: J8.2, R8.1
unnamed: J9.A5 (CC1), R11.1
unnamed: J9.B5 (CC2), R13.1
unnamed: C22.1, U1.8 (RCC_OSC32_IN), Y2.2
unnamed: C23.1, U1.9 (RCC_OSC32_OUT), Y2.1
unnamed: C20.2, U1.49 (VCAP_1)
unnamed: C21.1, U1.73 (VCAP_2)
unnamed: R2.1, U2.6 (CLK)
unnamed: C3.1, U3.1 (C1+)
unnamed: C3.2, U3.3 (C1-)
unnamed: C5.1, U3.4 (C2+)
unnamed: C5.2, U3.5 (C2-)
unnamed: C1.1, U3.2 (V+)
unnamed: C6.2, U3.6 (V-)
unnamed: C27.1, U4.5 (BP)

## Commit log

2025-07-12 Copied HID, pre-modification
2025-07-20 Now enumerating 2 USB devices
2025-07-21 First working with 2 devices
2025-07-22 Two interfaces enumerating
2025-07-22 Clean up object files from repo
2025-07-22 Add readme
2025-07-22 Clean up local settings directory
2025-07-23 Add: can disable/enable interface at boot
